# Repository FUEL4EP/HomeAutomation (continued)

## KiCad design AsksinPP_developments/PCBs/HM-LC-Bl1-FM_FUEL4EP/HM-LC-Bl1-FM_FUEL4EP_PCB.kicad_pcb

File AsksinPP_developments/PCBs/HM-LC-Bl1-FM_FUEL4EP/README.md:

# HM-LC-Bl1-FM_FUEL4EP   

**Platine für DIY AsksinPP für**
- 24V Polwendesteuerung für Velux Rolladen und Betrieb an einem Netzfreischalter
- Akkubetrieb im Standby, automatische Ladeschaltung
- am Beginn einer Rolladenfahrt wird die Netzspannung zugeschaltet und am Ende wieder abgeschaltet
- die Relay-Module werden mit 0,5mm² Adernendhülsen 'huckepack' auf die Platine gelötet, die Adernendhülsen zuerst auf die Relay-Module auflöten, dann in die Platine einstecken und in der Platine festlöten
- (fast) kein Standby-Verbrauch
- diese Schaltung und Platine darf ausschließlich von ausgebildeten elektrischen Fachkräften verwendet werden, siehe Disclaimer unten!
- diese Schaltung und Platine ist in der Version 1.0 validiert. Es sind aufgrund von Fehlern kleine Korrekturen vonnöten gewesen, die in der Version 1.3 korrigiert sind.
- ein geeigneter Sketch kann auf Nachfrage zur Verfügung gestellt werden.
    + per PN bei [FUEL4EP](https://homematic-forum.de/forum/ucp.php?i=pm&mode=compose&u=20685) im Homematic Forum nachfragen.
    + zur Zeit existiert ein funktionsfähiger Sketch, der noch um die Akkuladesoftware erweitert werden muss. Sobald die Entwicklung abgeschlossen sein wird, wird ein Release einschließlich Sketch auf Github gemacht werden.
- V1.3 der Platine behebt Fehler, die bei der Bestückung eines Prototypen erkannt wurden, bitte keine V1.0, V1.1 und V1.2 Platinen verwenden!
- **wichtige Aufbauhinweise:**
    + zuerst die Niederspannungsplatine HM-LC-Bl1-FM_FUEL4EP_PCB Schritt für Schritt aufbauen, in Betrieb nehmen und testen:
        + für den Arduino Pro Mini und den CC1101 Tranceiver **vor Einbau** in einem externen Testbed den Ruhestrom prüfen (<10uA) und einen Frequenztest durchführen!
        + das Modul 4 'LM2596 buck 24V->6.3V' zuerst außerhalb auf eine Ausgangsspannung von 6,3 Volt einstellen und dann erst einbauen!
    + die 230V Schaltungsteile erst dann anschließen, wenn der Rest vollständig geprüft wurde und die Software alle notwendigen Funktionen zeigt.
- Ein Diskussionsfaden ist im Homematic Forum unter [Nachbau HM-LC-Bl1-FM für Velux Rolladen und Netzfreischalter](https://homematic-forum.de/forum/viewtopic.php?f=76&t=71683&sid=71b7e84664ec8bed7b9e50bd442664ad) zu finden

## Versionen
- KiCad Schaltplan-Editor Version: 8.0.5-8.0.5-0~ubuntu22.04.1, release build unter Kubuntu22.04.1
- KiCad Leiterplatteneditor Version: 8.0.5-8.0.5-0~ubuntu22.04.1, release build unter Kubuntu22.04.1
- PCB Version 1.6 (Migration auf KiCAD 8 am 30. Sep 2024)
- PCB Schematics  1.4 (Migration auf KiCAD 8 am 30. Sep 2024)

## Disclaimer

- aufgrund der im Gerät frei geführten Netzspannung und des Netzspannungsanschlusses darf die Installation nur von Fachkräften durchgeführt werden, die aufgrund ihrer Ausbildung dazu befugt sind.
- die einschlägigen Sicherheits- und VDE-Bestimmungen sind unbedingt zu beachten. Durch eine unsachgemäße Installation können Sach- und Personenschäden verursacht werden, für die der Errichter haftet.
- Installationsarbeiten sowohl am primärseitigen Netzanschluss als auch am Sekundäranschluss dürfen nur **im stromlosen Zustand erfolgen. Dabei sind alle einschlägigen Vorschriften des Installationshandwerks zu beachten!** 
- die Nutzung der hier veröffentlichten Inhalte erfolgt vollständig auf eigenes Risiko und ohne jede Gewähr

## Lizenz 

**Creative Commons BY-NC-SA**<br>
Give Credit, NonCommercial, ShareAlike

<br />This work is licensed under a <a rel="license" href="http://creativecommons.org/licenses/by-nc-sa/4.0/">Creative Commons Attribution-NonCommercial-ShareAlike 4.0 International License</a>.

-EOF

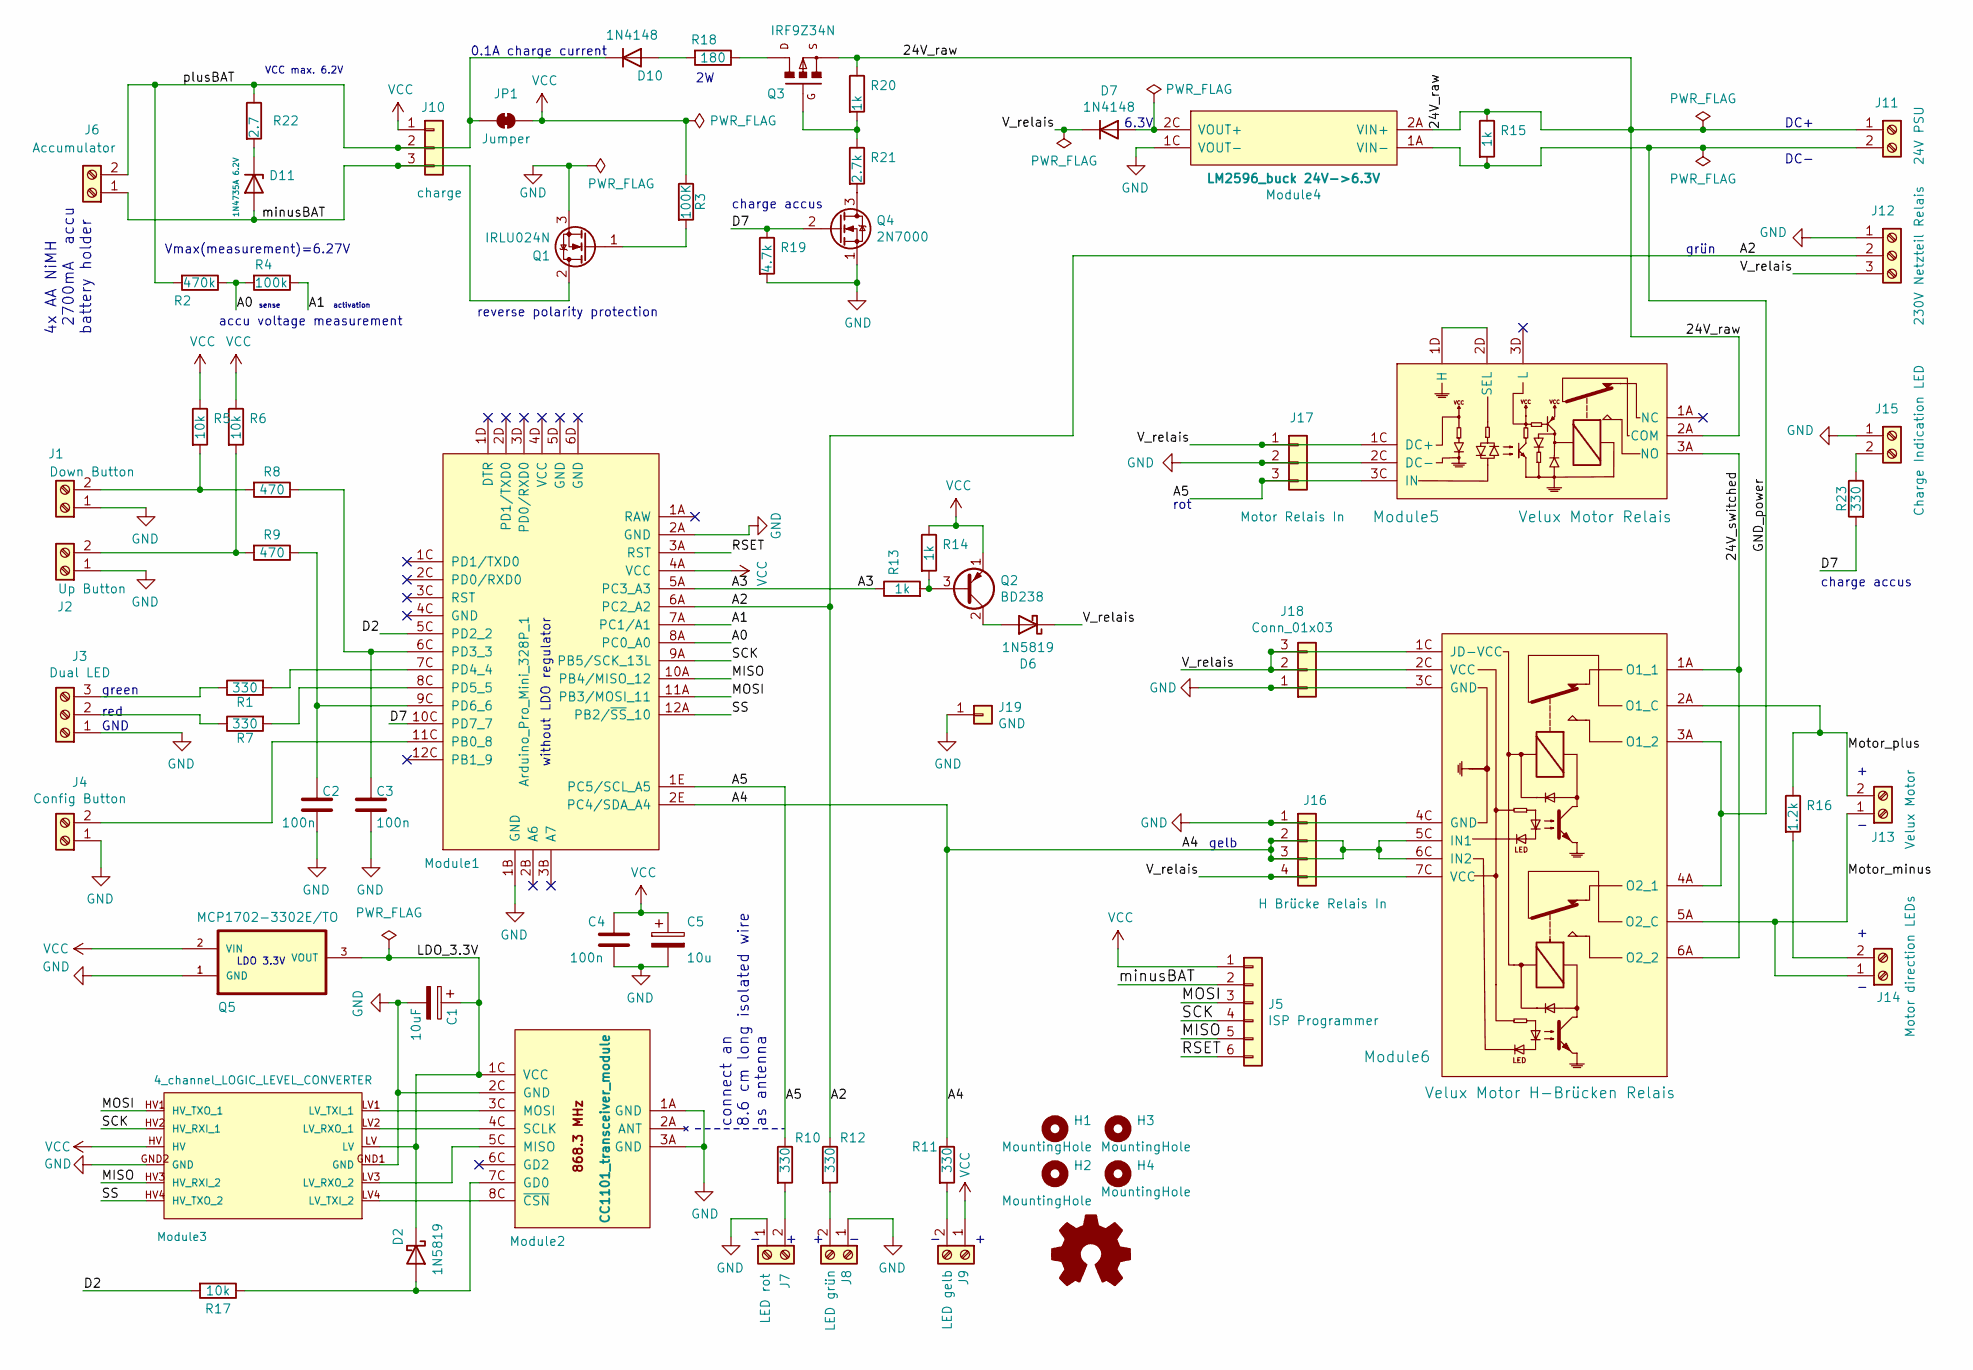
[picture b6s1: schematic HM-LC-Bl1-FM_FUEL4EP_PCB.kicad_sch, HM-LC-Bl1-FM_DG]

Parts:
C1: 10uF; CP_Radial_D5.0mm_P2.50mm
C2, C3, C4: 100n; C_Disc_D7.5mm_W2.5mm_P5.00mm
C5: 10u; CP_Radial_D5.0mm_P2.00mm
D2, D6: 1N5819; D_DO-41_SOD81_P10.16mm_Horizontal
D7, D10: 1N4148; D_DO-35_SOD27_P7.62mm_Horizontal
D11: 1N4735A 6.2V; D_DO-41_SOD81_P10.16mm_Horizontal
H1, H2, H3, H4: MountingHole; MountingHole_M3
J1: Down Button; TerminalBlock_Phoenix_MKDS-1,5-2-5.08_1x02_P5.08mm_Horizont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
J2: Up Button; TerminalBlock_Phoenix_MKDS-1,5-2-5.08_1x02_P5.08mm_Horizont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
J3: Dual LED; TerminalBlock_Phoenix_MKDS-1,5-3-5.08_1x03_P5.08mm_Horizont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
J4: Config Button; TerminalBlock_Phoenix_MKDS-1,5-2-5.08_1x02_P5.08mm_Horizont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
J5: ISP Programmer; PinHeader_1x06_P2.54mm_Vertical
J6: Accumulator; TerminalBlock_Phoenix_MKDS-1,5-2-5.08_1x02_P5.08mm_Horizont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
J7: LED rot; TerminalBlock_Phoenix_MKDS-1,5-2-5.08_1x02_P5.08mm_Horizont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
J8: LED grün; TerminalBlock_Phoenix_MKDS-1,5-2-5.08_1x02_P5.08mm_Horizont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
J9: LED gelb; TerminalBlock_Phoenix_MKDS-1,5-2-5.08_1x02_P5.08mm_Horizont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
J10: charge; PinHeader_1x03_P2.54mm_Vertical
J11: 24V PSU; TerminalBlock_Phoenix_MKDS-1,5-2-5.08_1x02_P5.08mm_Horizont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
J12: 230V Netzteil Relais; TerminalBlock_Phoenix_MKDS-1,5-3-5.08_1x03_P5.08mm_Horizont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
J13: Velux Motor; TerminalBlock_Phoenix_MKDS-1,5-2-5.08_1x02_P5.08mm_Horizont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
J14: Motor direction LEDs; TerminalBlock_Phoenix_MKDS-1,5-2-5.08_1x02_P5.08mm_Horizont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
J15: Charge Indication LED; TerminalBlock_Phoenix_MKDS-1,5-2-5.08_1x02_P5.08mm_Horizont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
J16: H Brücke Relais In; PinHeader_1x04_P2.54mm_Vertical
J17: Motor Relais In; PinHeader_1x03_P2.54mm_Vertical
J18: Conn_01x03; PinHeader_1x03_P2.54mm_Vertical
J19: GND; PinHeader_1x01_P1.27mm_Vertical
JP1: Jumper; SolderJumper-2_P1.3mm_Bridged2Bar_Pad1.0x1.5mm
LOGO1: Logo_Open_Hardware_Small; CC-BY-ND-SA
Module1: Arduino_Pro_Mini_328P_1; ArduinoProMini
Module2: CC1101_transceiver_module; CC1101
Module3: 4_channel_LOGIC_LEVEL_CONVERTER
Module4: LM2596_buck 24V->6.3V; LM2596_buck
Module5: Velux Motor Relais; 1_channel_relay_module
Module6: Velux Motor H-Brücken Relais; 2_channel_relay_module
Q1: IRLU024N; TO-251-3_Vertical
Q2: BD238; TO-126-3_Vertical
Q3: IRF9Z34N; TO220V
Q4: 2N7000; TO-92_Inline
Q5: MCP1702-3302E/TO; TO127P254X533-3
R1, R7, R10, R11, R12, R23: 330; R_Axial_DIN0204_L3.6mm_D1.6mm_P5.08mm_Horizontal
R2: 470k; R_Axial_DIN0204_L3.6mm_D1.6mm_P7.62mm_Horizontal
R3: 100K; R_Axial_DIN0204_L3.6mm_D1.6mm_P5.08mm_Horizontal
R4: 100k; R_Axial_DIN0204_L3.6mm_D1.6mm_P5.08mm_Horizontal
R5, R6, R17: 10k; R_Axial_DIN0204_L3.6mm_D1.6mm_P5.08mm_Horizontal
R8, R9: 470; R_Axial_DIN0204_L3.6mm_D1.6mm_P5.08mm_Horizontal
R13, R14, R15, R20: 1k; R_Axial_DIN0204_L3.6mm_D1.6mm_P5.08mm_Horizontal
R16: 1.2k; R_Axial_DIN0204_L3.6mm_D1.6mm_P5.08mm_Horizontal
R18: 180; R_Axial_DIN0614_L14.3mm_D5.7mm_P15.24mm_Horizontal
R19: 4.7k; R_Axial_DIN0204_L3.6mm_D1.6mm_P5.08mm_Horizontal
R21: 2.7k; R_Axial_DIN0204_L3.6mm_D1.6mm_P5.08mm_Horizontal
R22: 2.7; R_Axial_DIN0309_L9.0mm_D3.2mm_P12.70mm_Horizontal

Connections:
/24V_raw: J11.1, Module4.2A (VIN+), Module5.2A (COM), Q3.3, R15.1, R20.1
/24V_switched: Module5.3A (NO), Module6.1A (O1_1), Module6.6A (O2_2)
/A0: Module1.8A (PC0_A0), R2.1, R4.2
/A1: Module1.7A (PC1/A1), R4.1
/A2: J12.2, Module1.6A (PC2_A2), R12.1
/A3: Module1.5A (PC3_A3), R13.1
/A4: J16.2, J16.3, Module1.2E (PC4/SDA_A4), Module6.5C (IN1), Module6.6C (IN2), R11.1
/A5: J17.3, Module1.1E (PC5/SCL_A5), Module5.3C (IN), R10.1
/D2: Module1.5C (PD2_2), R17.2
/D7: Module1.10C (PD7_7), Q4.2 (G), R19.1, R23.2
/GND_power: J11.2, Module4.1A (VIN-), Module6.3A (O1_2), Module6.4A (O2_1), R15.2
/LDO_3.3V: C1.1, D2.1 (K), Module2.1C (VCC), Module3.LV, Q5.3 (VOUT)
/MISO: J5.5, Module1.10A (PB4/MISO_12), Module3.HV3 (HV_RXI_2)
/MOSI: J5.3, Module1.11A (PB3/MOSI_11), Module3.HV1 (HV_TXO_1)
/Motor_minus: J13.1, J14.1, Module6.5A (O2_C)
/Motor_plus: J13.2, Module6.2A (O1_C), R16.1
/RSET: J5.6, Module1.3A (RST)
/SCK: J5.4, Module1.9A (PB5/SCK_13L), Module3.HV2 (HV_RXI_1)
/SS: Module1.12A (PB2/~SS_10), Module3.HV4 (HV_TXO_2)
/V_relais: D6.1 (K), D7.1 (K), J12.3, J16.4, J17.1, J18.2, J18.3, Module5.1C (DC+), Module6.1C (JD-VCC), Module6.2C (VCC), Module6.7C (VCC)
/minusBAT: D11.2 (A), J5.2, J6.1, J10.3, Q1.2 (D)
/plusBAT: D10.1 (K), J6.2, J10.2, JP1.1 (A), R2.2, R22.1
GND: C1.2, C2.2, C3.2, C4.2, C5.2, J1.1, J2.1, J3.1, J4.1, J7.1, J8.1, J12.1, J15.1, J16.1, J17.2, J18.1, J19.1, Module1.1B (GND), Module1.2A (GND), Module2.1A (GND), Module2.2C (GND), Module2.3A (GND), Module3.GND1 (GND), Module3.GND2 (GND), Module4.1C (VOUT-), Module5.2C (DC-), Module6.3C (GND), Module6.4C (GND), Q1.3 (S), Q4.1 (S), Q5.1 (GND), R19.2
unnamed: D2.2 (A), Module2.7C (GD0), R17.1
unnamed: D6.2 (A), Q2.2 (C)
unnamed: D7.2 (A), Module4.2C (VOUT+)
unnamed: D10.2 (A), R18.2
unnamed: D11.1 (K), R22.2
unnamed: J1.2, R5.2, R8.2
unnamed: J2.2, R6.2, R9.2
unnamed: J3.2, R7.1
unnamed: J3.3, R1.1
unnamed: J4.2, Module1.11C (PB0_8)
unnamed: J7.2, R10.2
unnamed: J8.2, R12.2
unnamed: J9.2, R11.2
unnamed: J14.2, R16.2
unnamed: J15.2, R23.1
unnamed: C3.1, Module1.6C (PD3_3), R8.1
unnamed: Module1.7C (PD4_4), R1.2
unnamed: Module1.8C (PD5_5), R7.2
unnamed: C2.1, Module1.9C (PD6_6), R9.1
unnamed: Module2.5C (MISO), Module3.LV3 (LV_RXO_2)
unnamed: Module2.3C (MOSI), Module3.LV1 (LV_TXI_1)
unnamed: Module2.4C (SCLK), Module3.LV2 (LV_RXO_1)
unnamed: Module2.8C (~CSN), Module3.LV4 (LV_TXI_2)
unnamed: Module5.1D (H), Module5.2D (SEL)
unnamed: Q1.1 (G), R3.2
unnamed: Q2.3 (B), R13.2, R14.2
unnamed: Q3.1, R20.2, R21.1
unnamed: Q3.2, R18.1
unnamed: Q4.3 (D), R21.2
VCC: C4.1, C5.1, J5.1, J9.1, J10.1, JP1.2 (B), Module1.4A (VCC), Module3.HV, Q2.1 (E), Q5.2 (VIN), R3.1, R5.1, R6.1, R14.1

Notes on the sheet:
DC+
rot
charge accus
GND
green
accu voltage measurement
VCC max. 6.2V
red
connect an 8.6 cm long isolated wire as antenna
4x AA NiMH 2700mA accu battery holder
grün
reverse polarity protection
0.1A charge current
without LDO regulator
activation
6.3V
Vmax(measurement)=6.27V
LDO 3.3V
DC-
gelb
sense

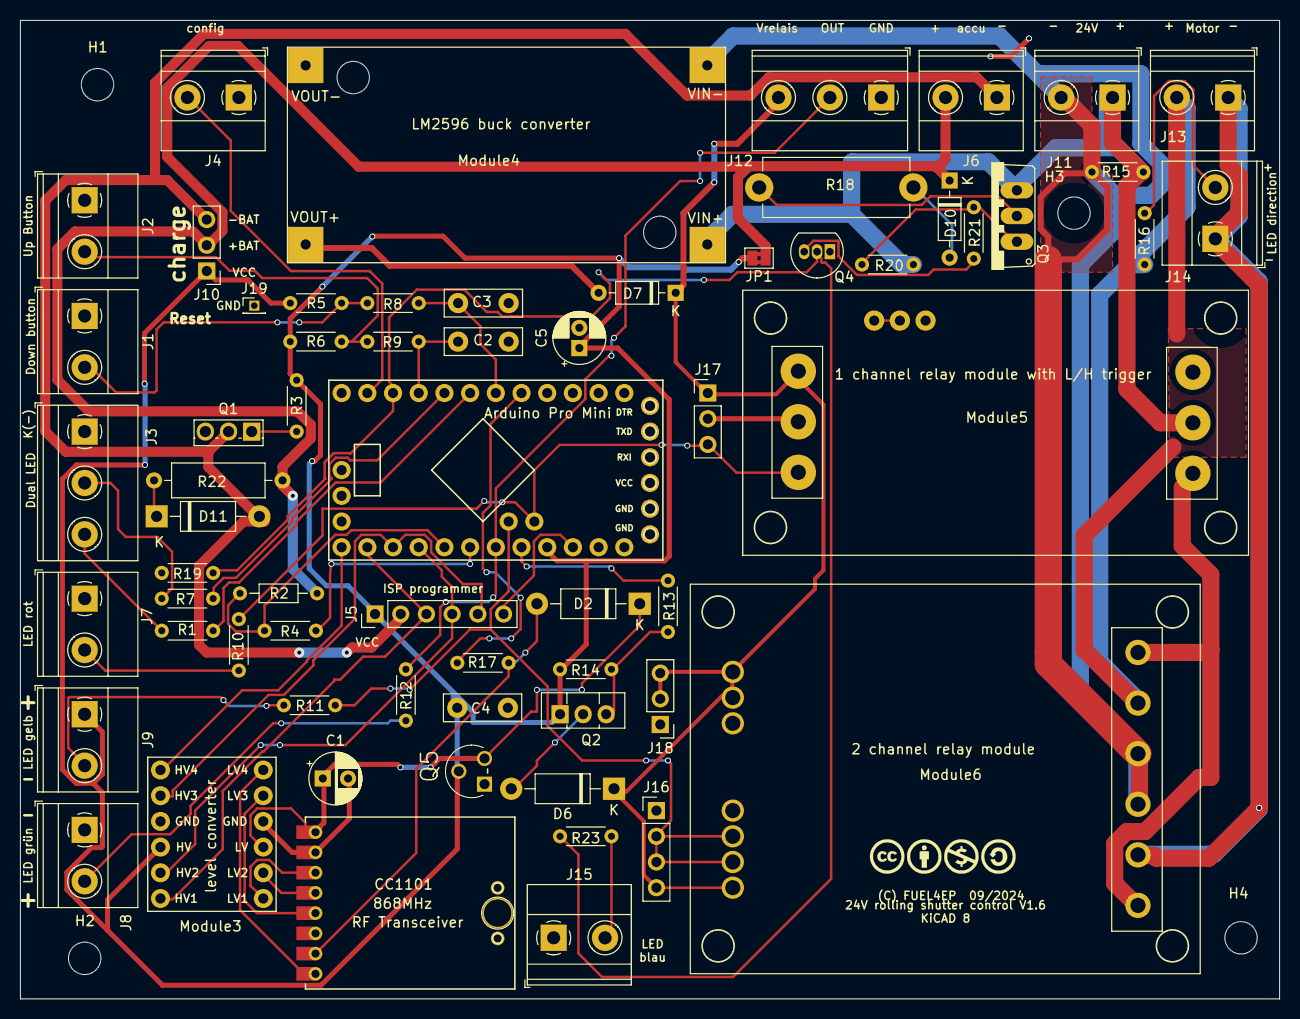
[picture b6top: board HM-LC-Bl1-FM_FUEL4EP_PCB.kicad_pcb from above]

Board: 2 copper layers, 124.5 x 96.7 mm, 69 parts (0 on the bottom side), 53 nets.

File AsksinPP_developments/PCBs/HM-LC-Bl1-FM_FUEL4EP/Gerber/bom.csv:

Designator,Footprint,Quantity,Value,LCSC Part #
C1,CP_Radial_D5.0mm_P2.50mm,1,10uF,
"C2, C3, C4",C_Disc_D7.5mm_W2.5mm_P5.00mm,3,100n,
C5,CP_Radial_D5.0mm_P2.00mm,1,10u,
"D10, D7",D_DO-35_SOD27_P7.62mm_Horizontal,2,1N4148,
D11,D_DO-41_SOD81_P10.16mm_Horizontal,1,1N4735A 6.2V,
"D2, D6",D_DO-41_SOD81_P10.16mm_Horizontal,2,1N5819,
"H1, H2, H3, H4",MountingHole_M3,4,MountingHole,
J1,"TerminalBlock_Phoenix_MKDS-1,5-2-5.08_1x02_P5.08mm_Horizontal",1,Down Button,
J10,PinHeader_1x03_P2.54mm_Vertical,1,charge,
J11,"TerminalBlock_Phoenix_MKDS-1,5-2-5.08_1x02_P5.08mm_Horizontal",1,24V PSU,
J12,"TerminalBlock_Phoenix_MKDS-1,5-3-5.08_1x03_P5.08mm_Horizontal",1,230V Netzteil Relais,
J13,"TerminalBlock_Phoenix_MKDS-1,5-2-5.08_1x02_P5.08mm_Horizontal",1,Velux Motor,
J14,"TerminalBlock_Phoenix_MKDS-1,5-2-5.08_1x02_P5.08mm_Horizontal",1,Motor direction LEDs,
J15,"TerminalBlock_Phoenix_MKDS-1,5-2-5.08_1x02_P5.08mm_Horizontal",1,Charge Indication LED,
J16,PinHeader_1x04_P2.54mm_Vertical,1,H Brücke Relais In,
J17,PinHeader_1x03_P2.54mm_Vertical,1,Motor Relais In,
J18,PinHeader_1x03_P2.54mm_Vertical,1,Conn_01x03,
J19,PinHeader_1x01_P1.27mm_Vertical,1,GND,
J2,"TerminalBlock_Phoenix_MKDS-1,5-2-5.08_1x02_P5.08mm_Horizontal",1,Up Button,
J3,"TerminalBlock_Phoenix_MKDS-1,5-3-5.08_1x03_P5.08mm_Horizontal",1,Dual LED,
J4,"TerminalBlock_Phoenix_MKDS-1,5-2-5.08_1x02_P5.08mm_Horizontal",1,Config Button,
J5,PinHeader_1x06_P2.54mm_Vertical,1,ISP Programmer,
J6,"TerminalBlock_Phoenix_MKDS-1,5-2-5.08_1x02_P5.08mm_Horizontal",1,Accumulator,
J7,"TerminalBlock_Phoenix_MKDS-1,5-2-5.08_1x02_P5.08mm_Horizontal",1,LED rot,
J8,"TerminalBlock_Phoenix_MKDS-1,5-2-5.08_1x02_P5.08mm_Horizontal",1,LED grün,
J9,"TerminalBlock_Phoenix_MKDS-1,5-2-5.08_1x02_P5.08mm_Horizontal",1,LED gelb,
JP1,SolderJumper-2_P1.3mm_Bridged2Bar_Pad1.0x1.5mm,1,Jumper,
LOGO1,CC-BY-ND-SA,1,Logo_Open_Hardware_Small,
Module1,ArduinoProMini,1,Arduino_Pro_Mini_328P_1,
Module2,CC1101,1,CC1101_transceiver_module,
Module3,4_channel_LOGIC_LEVEL_CONVERTER,1,>VALUE,
Module4,LM2596_buck,1,LM2596_buck 24V->6.3V,
Module5,1_channel_relay_module,1,Velux Motor Relais,
Module6,2_channel_relay_module,1,Velux Motor H-Brücken Relais,
Q1,TO-251-3_Vertical,1,IRLU024N,
Q2,TO-126-3_Vertical,1,BD238,
Q3,TO220V,1,IRF9Z34N,
Q4,TO-92_Inline,1,2N7000,
Q5,TO127P254X533-3,1,MCP1702-2802E_TO,MCP1702-2802E/TO
"R1, R10, R11, R12, R23, R7",R_Axial_DIN0204_L3.6mm_D1.6mm_P5.08mm_Horizontal,6,330,
"R13, R14, R15, R20",R_Axial_DIN0204_L3.6mm_D1.6mm_P5.08mm_Horizontal,4,1k,
R16,R_Axial_DIN0204_L3.6mm_D1.6mm_P5.08mm_Horizontal,1,1.2k,
"R17, R5, R6",R_Axial_DIN0204_L3.6mm_D1.6mm_P5.08mm_Horizontal,3,10k,
R18,R_Axial_DIN0614_L14.3mm_D5.7mm_P15.24mm_Horizontal,1,180,
R19,R_Axial_DIN0204_L3.6mm_D1.6mm_P5.08mm_Horizontal,1,4.7k,
R2,R_Axial_DIN0204_L3.6mm_D1.6mm_P7.62mm_Horizontal,1,470k,
R21,R_Axial_DIN0204_L3.6mm_D1.6mm_P5.08mm_Horizontal,1,2.7k,
R22,R_Axial_DIN0309_L9.0mm_D3.2mm_P12.70mm_Horizontal,1,2.7,
"R3, R4",R_Axial_DIN0204_L3.6mm_D1.6mm_P5.08mm_Horizontal,2,100K,
"R8, R9",R_Axial_DIN0204_L3.6mm_D1.6mm_P5.08mm_Horizontal,2,470,

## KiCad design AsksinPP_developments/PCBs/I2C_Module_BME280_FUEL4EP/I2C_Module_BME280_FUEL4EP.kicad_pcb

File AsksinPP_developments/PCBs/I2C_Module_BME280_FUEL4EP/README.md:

# I2C_Module_BME280_FUEL4EP  

# Warnung: Diese Version der Platine ist noch nicht valdiert. Nutzung auf eigenes Risiko!

## I2C BME280 Sensor Aufsteckplatine für DIY AsksinPP-Projekte

- basierend auf [Bosch BME280](https://www.bosch-sensortec.com/media/boschsensortec/downloads/datasheets/bst-bme280-ds002.pdf)

- passend zu
	* [HB-UNI-SEN-BATT_ATMega1284P_E07-868MS10_FUEL4EP](https://github.com/FUEL4EP/HomeAutomation/tree/master/AsksinPP_developments/PCBs/HB-UNI-SEN-BATT_ATMega1284P_E07-868MS10_FUEL4EP)
	* [HB-UNI-SEN-BATT_ATMega1284P_E07-868MS10_FRAM_FUEL4EP](https://github.com/FUEL4EP/HomeAutomation/tree/master/AsksinPP_developments/PCBs/HB-UNI-SEN-BATT_ATMega1284P_E07-868MS10_FRAM_FUEL4EP)
	* [HB-UNI-SEN-BATT_FUEL4EP](https://github.com/FUEL4EP/HomeAutomation/tree/master/AsksinPP_developments/PCBs/HB-UNI-SEN-BATT_FUEL4EP)
	* [HB-UNI-SEN-BATT_ATMega1284P_E07-868MS10_FUEL4EP](https://github.com/FUEL4EP/HomeAutomation/tree/master/AsksinPP_developments/PCBs/HB-UNI-SEN-BATT_ATMega1284P_E07-868MS10_FUEL4EP)
	* Befestigung mit 2 Stiftleisten J1 und J2
	
- VCC max. ist 3,3 Volt !!
- die voreingestellte Standard-I2C-Adresse ist 0x76
- für die I2C-Adresse 0x77 ist der Jumper JP1 aufzutrennen und der Jumper JP2 mit Lötzinn zu überbrücken

- Infos zu AsksinPP sind [hier](https://asksinpp.de) und [hier](https://asksinpp.de/Grundlagen/01_hardware.html#verdrahtung) zu finden

## Platinenmaße

- Breite: 30,48 mm
- Weite: 17 mm
- Platinendicke 1,6 mm (bei der Bestellung bei JLCPCB auswählen)

## Stromlaufplan

- ist [hier](./Schematics/I2C_Module_BME280_FUEL4EP.pdf)

## Status

- diese Platine wurde noch nicht bei JLCPCB gefertigt und ist daher auch nicht validiert. Nutzung auf eigenes Risiko!

## Rückmeldungen

- und Verbesserungsvorschläge sind willkommen.

### KiCAD Plugin
- für die Erzeugung der JLCPCB Produktionsdaten wurde das Plugin [KiCAD JLCPCB tools](https://github.com/bouni/kicad-jlcpcb-tools) verwendet.

## Daten für die Bestellung bei JLCPCB

- die Daten für die Bestellung liegen im Verzeichnis [./jlcpcb/production_files/](./jlcpcb/production_files/)
- Gerber-Daten als Zip-Datei
- BOM- und CPL-Daten als CSV-Datei

- die Rotation von U1 (BME280) ist bei JLCPCB Assembly-Service-Online-View falsch und muss händisch korrigiert und geprüft werden. Bitte die entsprechende Option beim Bestellen wählen.

## lokale Installation des Github Releases auf Deinem Computer

- gehe bitte in Dein Zielinstallationsverzeichnis, wo Du mit der I2C_Module_BME280_FUEL4EP Platine mit KiCAD arbeiten möchtest

  - gebe dort 'git clone https://github.com/FUEL4EP/HomeAutomation.git' ein
	  + damit lädst Du mein [Sammelrepository](https://github.com/FUEL4EP/HomeAutomation) für alle meine auf Github freigegebenen HomeBrew Entwicklungen herunter.
  - dann findest Du ein neues Verzeichnis 'HomeAutomation' auf Deinem Rechner, das alle meine auf Github freigebenen Entwicklungen enthält, siehe [README.md](https://github.com/FUEL4EP/HomeAutomation/blob/master/README.md)
  	+ mache bitte regelmäßig ein Update mit 'git pull'
 -	die Platine I2C_Module_BME280_FUEL4EP findest Du unter './HomeAutomation/tree/master/AsksinPP_developments/PCBs/I2C_Module_BME280_FUEL4EP'
 
- alternativ kann vom Github [Sammelrepository](https://github.com/FUEL4EP/HomeAutomation) die ZIP-Datei HomeAutomation-master.zip heruntergeladen und auf dem lokalen Rechner ausgepackt werden. Bitte dann regelmäßig auf Github nach Updates schauen.

## Versionsverlauf

-   V1.0 07. Sep 2023: Initiale Veröffentlichung auf Github
-	V1.1 15. Dez 2023: korrigierte Platzierung der Stiftleisten in der 3D-Ansicht
-	S V1.3 08. Feb 2024: Fix der I2C Pull-Up Widerstände
-	L V1.2 08. Feb 2024: Fix der I2C Pull-Up Widerstände
-	S V1.4 16. Apr 2024: Ersetzen von R3 durch JP2 wegen Ruhestrom; Migration auf KiCAD 7
-	L V1.3 16. Apr 2024: Ersetzen von R3 durch JP2 wegen Ruhestrom; Migration auf KiCAD 7
-	S V1.5 30. Sep 2024: Migration auf KiCAD 8
-	L V1.4 30. Sep 2024: Migration auf KiCAD 8
- KiCad Schaltplan-Editor Version: 8.0.5-8.0.5-0~ubuntu22.04.1, release build unter Kubuntu22.04.4
- KiCad Leiterplatteneditor Version: 8.0.5-8.0.5-0~ubuntu22.04.1, release build unter Kubuntu22.04.4
- PCB Version 1.4
- Schematics  1.5

## Disclaimer

-   die Nutzung der hier veröffentlichten Inhalte erfolgt vollständig auf eigenes Risiko und ohne jede Gewähr.

## Lizenz 

**Creative Commons BY-NC-SA**<br>
Give Credit, NonCommercial, ShareAlike

<br />This work is licensed under a <a rel="license" href="http://creativecommons.org/licenses/by-nc-sa/4.0/">Creative Commons Attribution-NonCommercial-ShareAlike 4.0 International License</a>.

-EOF

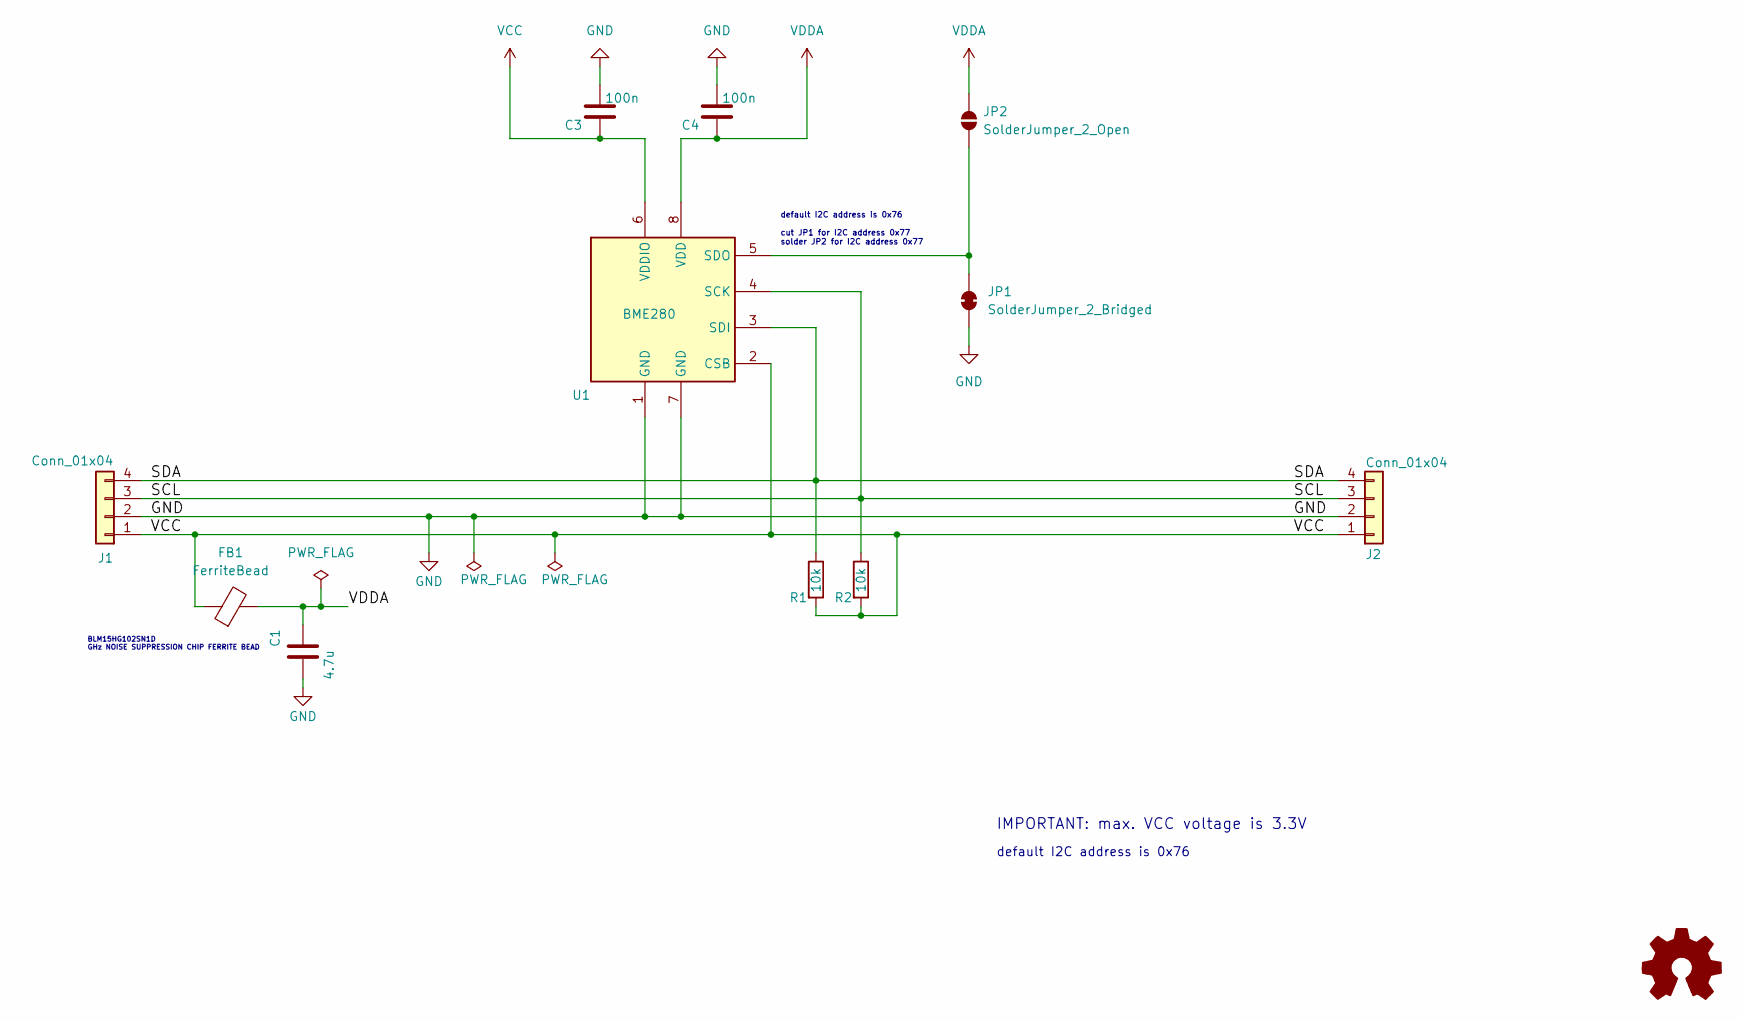
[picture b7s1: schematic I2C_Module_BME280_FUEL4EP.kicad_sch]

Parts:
C1: 4.7u; C_0603_1608Metric; LCSC C19666
C3, C4: 100n; C_0603_1608Metric; LCSC C14663
FB1: FerriteBead; L_0402_1005Metric; LCSC C76889
J1, J2: Conn_01x04; PinHeader_1x04_P2.54mm_Vertical
JP1: SolderJumper_2_Bridged; SolderJumper-2_P1.3mm_Bridged_Pad1.0x1.5mm
JP2: SolderJumper_2_Open; SolderJumper-2_P1.3mm_Open_Pad1.0x1.5mm
LOGO1: Logo_Open_Hardware_Small; CC-BY-ND-SA
R1, R2: 10k; R_0402_1005Metric; LCSC C25744
U1: BME280; Bosch_LGA-8_2.5x2.5mm_P0.65mm_ClockwisePinNumbering; LCSC C92489

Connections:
/SCL: J1.3, J2.3, R2.1, U1.4 (SCK)
/SDA: J1.4, J2.4, R1.1, U1.3 (SDI)
GND: C1.2, C3.1, C4.1, J1.2, J2.2, JP1.1 (A), U1.1 (GND), U1.7 (GND)
unnamed: JP1.2 (B), JP2.1 (A), U1.5 (SDO)
VCC: C3.2, FB1.1, J1.1, J2.1, R1.2, R2.2, U1.2 (CSB), U1.6 (VDDIO)
VDDA: C1.1, C4.2, FB1.2, JP2.2 (B), U1.8 (VDD)

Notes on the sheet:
cut JP1 for I2C address 0x77
BLM15HG102SN1D GHz NOISE SUPPRESSION CHIP FERRITE BEAD
default I2C address is 0x76
solder JP2 for I2C address 0x77
IMPORTANT: max. VCC voltage is 3.3V

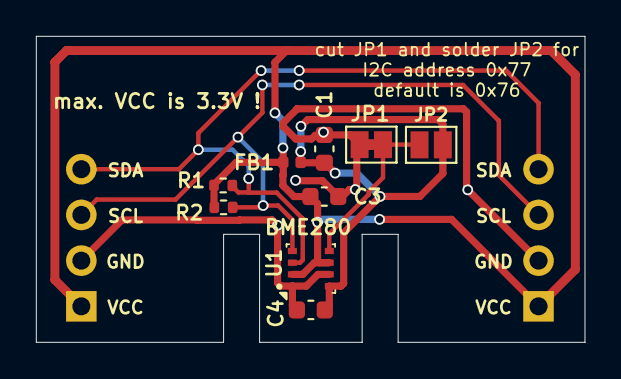
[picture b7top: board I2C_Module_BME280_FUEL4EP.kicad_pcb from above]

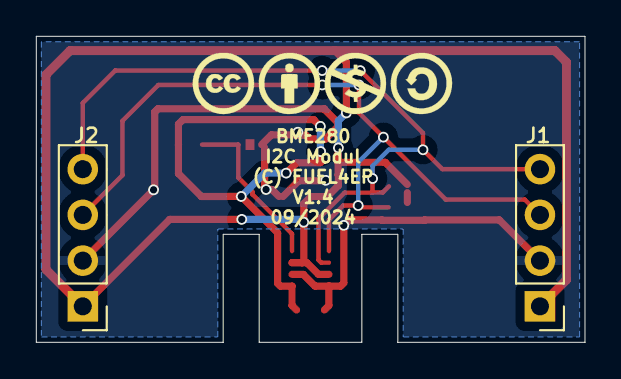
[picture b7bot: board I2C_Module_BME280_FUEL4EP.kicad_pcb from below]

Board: 2 copper layers, 30.5 x 17.0 mm, 12 parts (3 on the bottom side), 6 nets.
